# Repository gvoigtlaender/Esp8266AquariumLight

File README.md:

# Esp8266AquariumLight
## ESP8266, KSQ-1A, LM2576S, PWM

## Project goals:
* time-based control of 2 separate PWM channels to adjust LED light intensity
* small footprint to integrate into given aquarium cover (max hight: 30mm)
* generate all voltages from given 12V supply
* onboard programmer interface (RX/TX, buttons)
* support for available constant power supply modules (KSQ 1A, pin-compatible to add-on)
* support external button to switch states
* support external button LED light to indicate states
* optional ONEWIRE temperature sensor (e.g. DS18B20)
* optional FAN output (switchable)

## Used items:
* LM2576S Step-Down (12V -> 5V)
* AMS1117-3.3 LDO (5V -> 3.3V)
* ESP8266 (ESP-12F) as CPU
* general purpose MOSFET & BJT
* resistors, capacitory (SMD 0805)

## Schematic:

## PCB:

## Assembly

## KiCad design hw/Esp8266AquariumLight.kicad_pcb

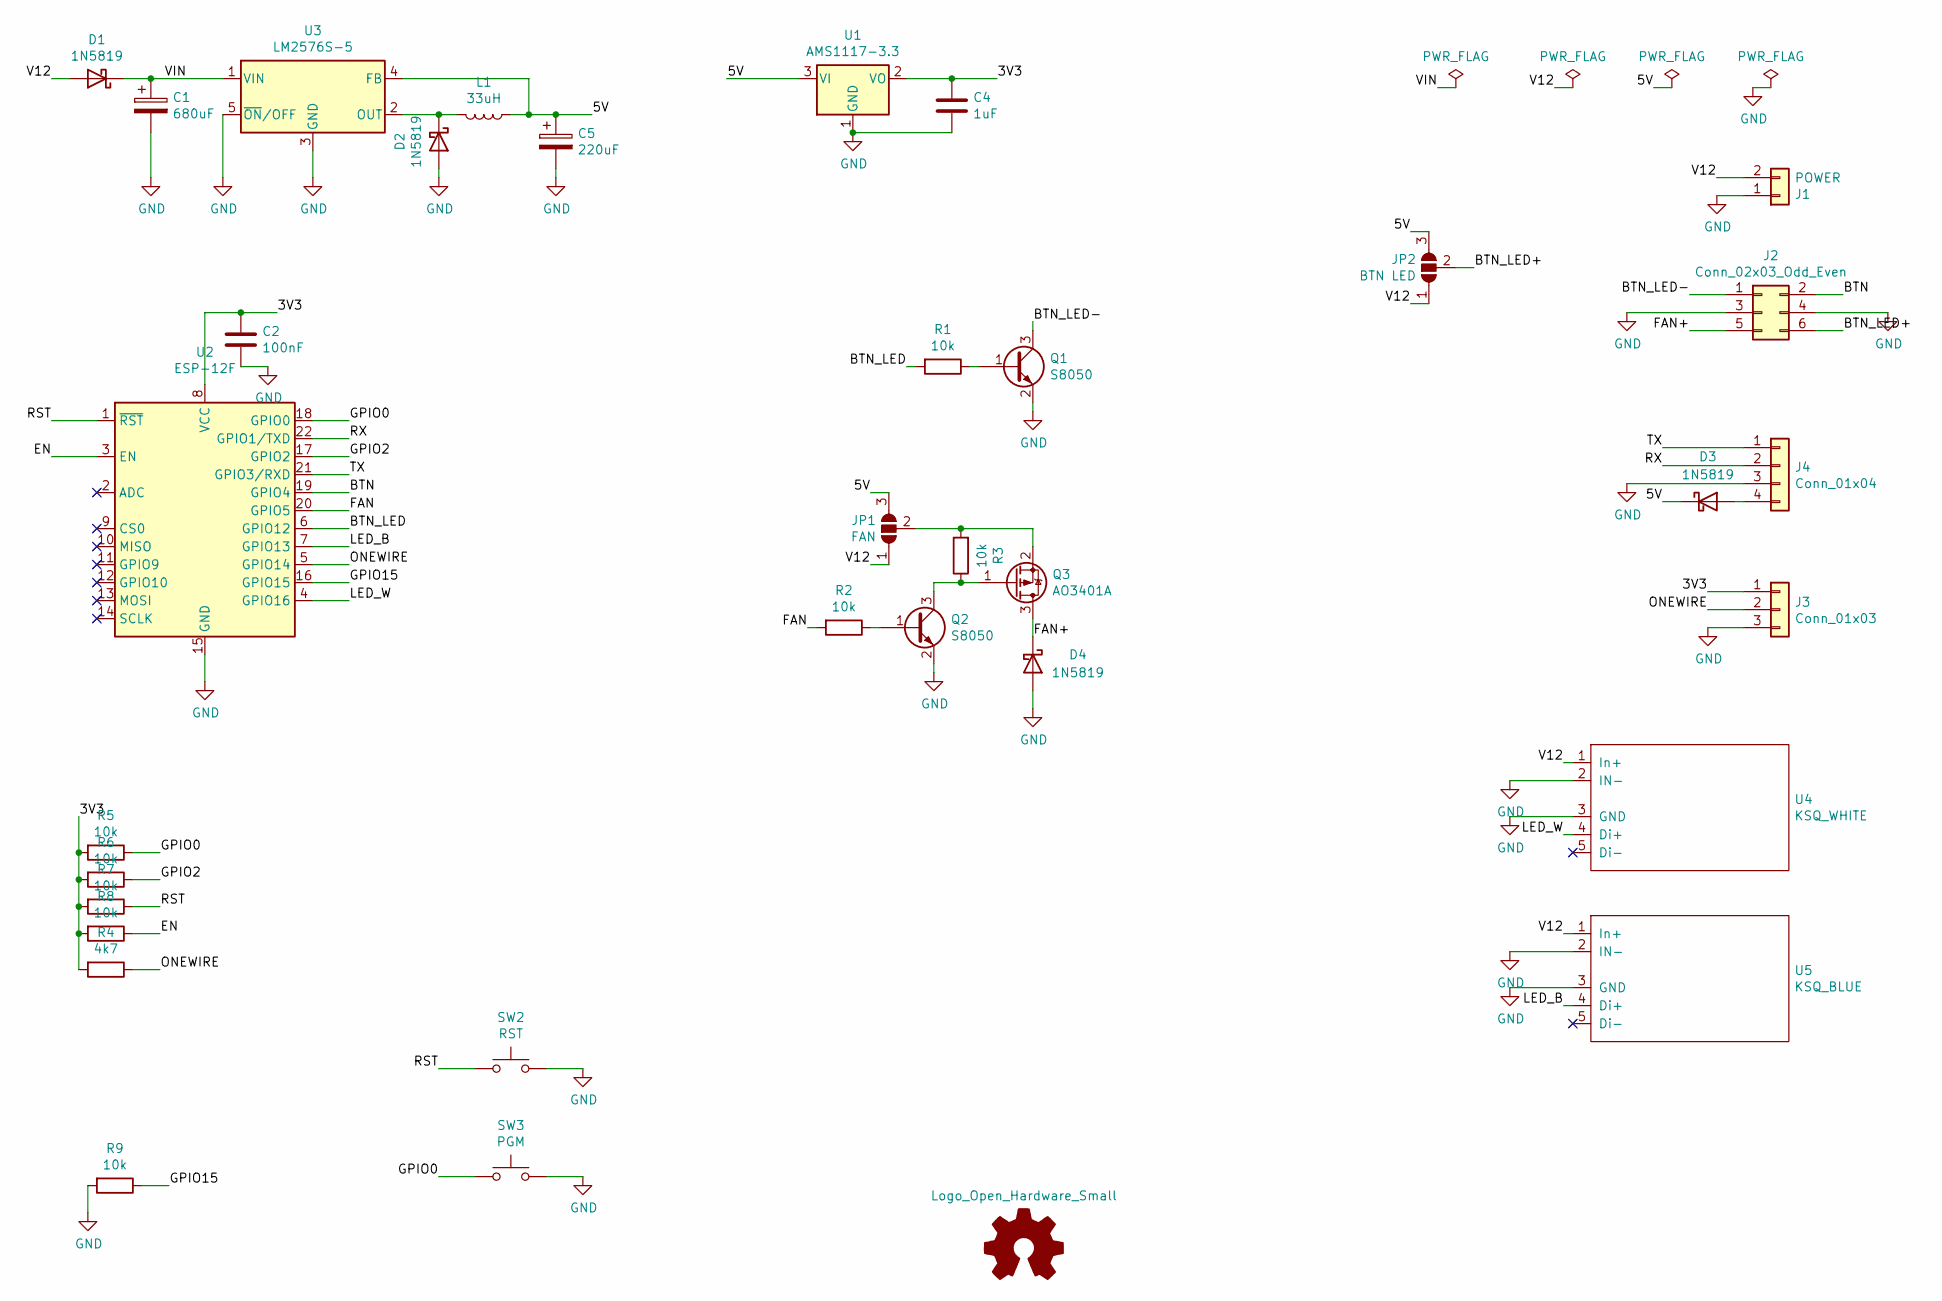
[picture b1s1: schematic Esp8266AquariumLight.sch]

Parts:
C1: 680uF; CP_Radial_D8.0mm_P2.50mm
C2: 100nF; C_0805_2012Metric
C4: 1uF; C_0805_2012Metric
C5: 220uF; CP_Radial_D5.0mm_P2.50mm
D1, D2, D3, D4: 1N5819; D_SMA
J1: POWER; JST_NV_B02P-NV_1x02_P5.00mm_Vertical
J2: Conn_02x03_Odd_Even; PinHeader_2x03_P2.54mm_Horizontal
J3: Conn_01x03; PinHeader_1x03_P2.54mm_Horizontal
J4: Conn_01x04; JSTPH4
JP1: FAN; SolderJumper-3_P1.3mm_Open_RoundedPad1.0x1.5mm
JP2: BTN LED; SolderJumper-3_P1.3mm_Open_RoundedPad1.0x1.5mm
L1: 33uH; L_12x12mm_Flexible_H8mm
Q1, Q2: S8050; SOT-23
Q3: AO3401A; SOT-23
R1, R2, R3, R5, R6, R7, R8, R9: 10k; R_0805_2012Metric
R4: 4k7; R_0805_2012Metric
SW2: RST; SW_SPST_SKQG_WithoutStem
SW3: PGM; SW_SPST_SKQG_WithoutStem
U1: AMS1117-3.3; SOT-223-3_TabPin2
U2: ESP-12F; ESP-12E
U3: LM2576S-5; TO-263-5_TabPin3
U4: KSQ_WHITE; KSQ_1000mA
U5: KSQ_BLUE; KSQ_1000mA

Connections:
/3V3: C2.1, C4.1, J3.1, R4.2, R5.2, R6.2, R7.2, R8.2, U1.2 (VO), U2.8 (VCC)
/5V: C5.1, D3.1 (K), JP1.3 (B), JP2.3 (B), L1.1, U1.3 (VI), U3.4 (FB)
/BTN: J2.2, U2.19 (GPIO4)
/BTN_LED: R1.2, U2.6 (GPIO12)
/BTN_LED+: J2.6, JP2.2 (C)
/BTN_LED-: J2.1, Q1.3 (C)
/EN: R8.1, U2.3 (EN)
/FAN: R2.2, U2.20 (GPIO5)
/FAN+: D4.1 (K), J2.5, Q3.3 (D)
/GPIO0: R5.1, SW3.1, U2.18 (GPIO0)
/GPIO2: R6.1, U2.17 (GPIO2)
/GPIO15: R9.1, U2.16 (GPIO15)
/LED_B: U2.7 (GPIO13), U5.4 (Di+)
/LED_W: U2.4 (GPIO16), U4.4 (Di+)
/ONEWIRE: J3.2, R4.1, U2.5 (GPIO14)
/RST: R7.1, SW2.1, U2.1 (~RST)
/RX: J4.2, U2.22 (GPIO1/TXD)
/TX: J4.1, U2.21 (GPIO3/RXD)
/V12: D1.2 (A), J1.2, JP1.1 (A), JP2.1 (A), U4.1 (In+), U5.1 (In+)
/VIN: C1.1, D1.1 (K), U3.1 (VIN)
GND: C1.2, C2.2, C4.2, C5.2, D2.2 (A), D4.2 (A), J1.1, J2.3, J2.4, J3.3, J4.3, Q1.2 (E), Q2.2 (E), R9.2, SW2.2, SW3.2, U1.1 (GND), U2.15 (GND), U3.3 (GND), U3.5 (~ON~/OFF), U4.2 (IN-), U4.3 (GND), U5.2 (IN-), U5.3 (GND)
unnamed: D2.1 (K), L1.2, U3.2 (OUT)
unnamed: D3.2 (A), J4.4
unnamed: JP1.2 (C), Q3.2 (S), R3.2
unnamed: Q1.1 (B), R1.1
unnamed: Q2.1 (B), R2.1
unnamed: Q2.3 (C), Q3.1 (G), R3.1

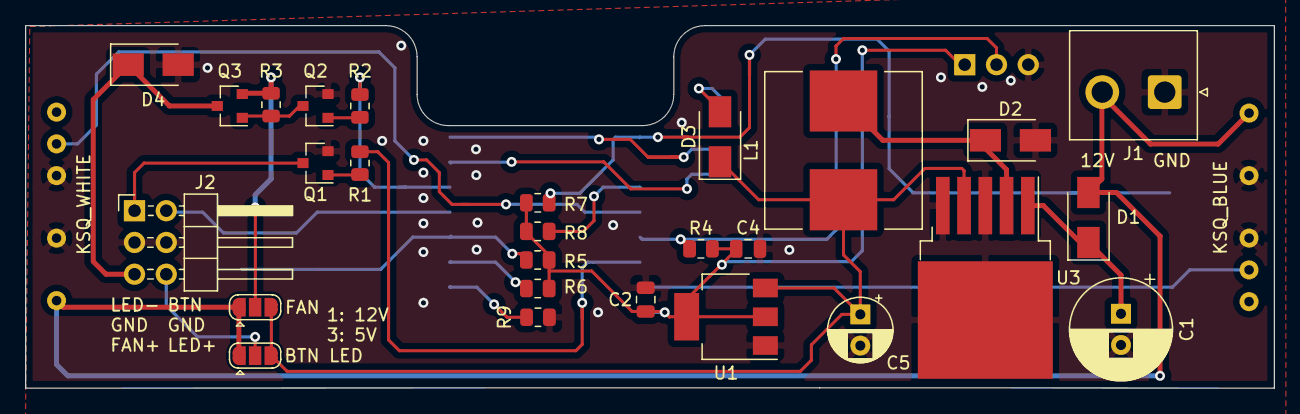
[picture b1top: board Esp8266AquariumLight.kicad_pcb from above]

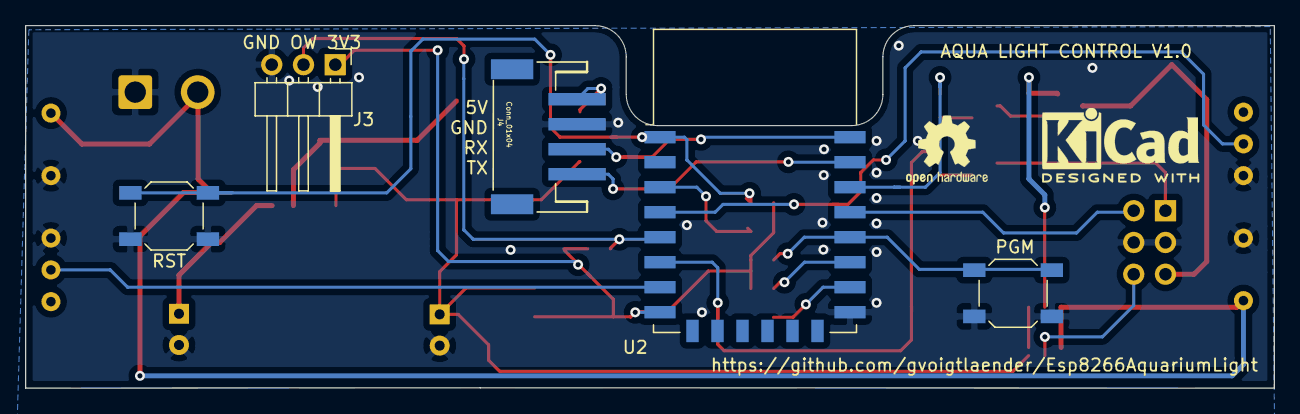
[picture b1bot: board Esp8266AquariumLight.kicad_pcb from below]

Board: 2 copper layers, 99.9 x 29.0 mm, 34 parts (5 on the bottom side), 27 nets.

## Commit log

2021-11-29 Update .gitignore
    empy
2021-11-29 add code
2021-11-29 add hw
2021-11-29 update: readme
2021-11-29 add config.h
2021-12-23 update: mqtt CmdAuto/White/Blue/Off
2021-12-25 update: assembly pictures
2021-12-27 update: version strings update: show mqtt state update: export TimeToChange as string
2022-01-25 add 1ch implementation
2022-01-25 bugfix: use double values
2022-01-29 add: ButtonOffAutoMode (no looping A>B>W>O) update: TimeToChange for Fading
2022-01-29 update: correct TimeToChange while fading
2022-02-01 update: disable noon mode
